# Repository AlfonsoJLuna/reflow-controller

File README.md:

# Reflow Controller

Open-source reflow controller for ovens and hot plates.

 | 
:---: | :---:
Front | Back

## Features

* MCU: STM32G030K6T6
* CH340E USB-Serial converter.
* Sensors: K-Type thermocouple to digital converter. Compatible with both MAX31855 and MAX6675.
* Display: SSD1306 128×164 0.96" OLED.
* Inputs: 4x Push buttons to navigate the menu.
* Outputs: 2x 5V 300mA outputs. Capable of driving solid state relays as well as inductive loads (mechanical relays, fans).
* Buzzer: Alarm buzzer.
* Power: 5V provided via USB-C or screw terminals.

## Related repositories

Firmware for this project lives in [reflow-controller-fw](https://github.com/AlfonsoJLuna/reflow-controller-fw).

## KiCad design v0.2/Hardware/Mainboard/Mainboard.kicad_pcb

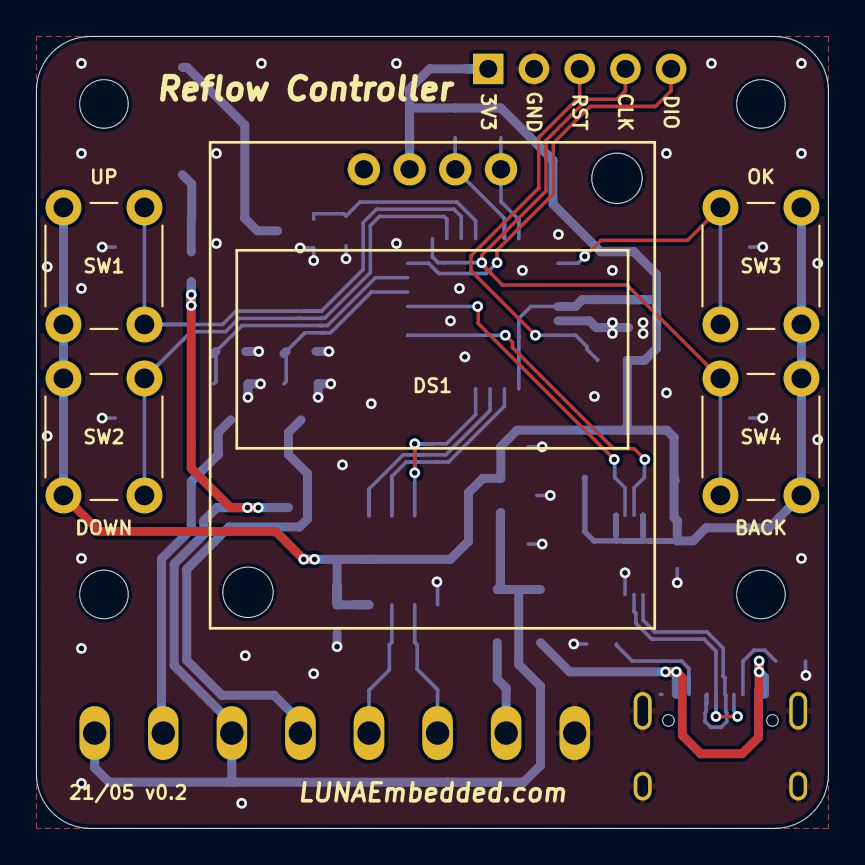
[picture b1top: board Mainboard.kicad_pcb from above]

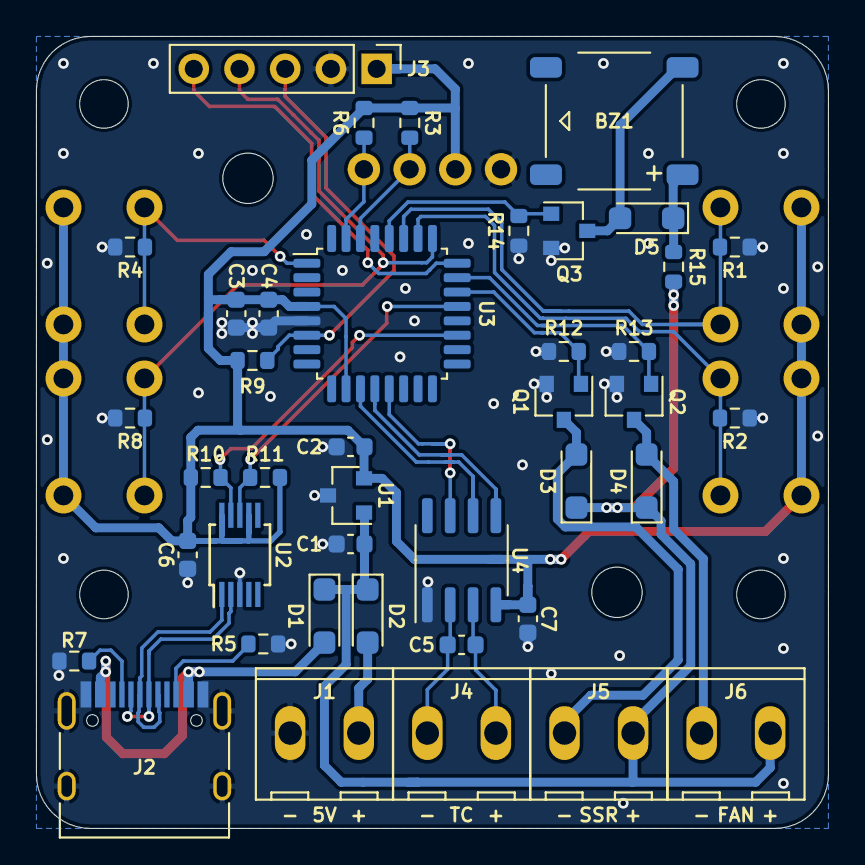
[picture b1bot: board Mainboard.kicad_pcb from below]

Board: 2 copper layers, 44.0 x 44.0 mm, 46 parts (41 on the bottom side), 31 nets.

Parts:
BZ1: MLT-7525
C1, C2, C3: 10u; C_0603_1608Metric
C4, C6, C7: 100n; C_0603_1608Metric
C5: 10n; C_0603_1608Metric
D1, D2, D3, D4, D5: MBR120VLSFT3G; SOD-123FL
DS1: SSD1306_0.96_128x64_I2C
J1: 5V; WJ124-3.81-2P
J2: TYPE-C-31-M-12; USB_C_Receptacle_HRO_TYPE-C-31-M-12
J3: Debug; PinHeader_1x05_P2.54mm_Vertical
J4: TC; WJ124-3.81-2P
J5: S1; WJ124-3.81-2P
J6: S2; WJ124-3.81-2P
Q1, Q2, Q3: BSS138P; SOT-23
R1, R2, R4, R5, R7, R8, R9, R12, R13, R14: 5K1; R_0603_1608Metric
R3, R6, R10, R11: DNP; R_0603_1608Metric
R15: 100; R_0603_1608Metric
SW1: UP; SW_PUSH_6mm_H9.5mm
SW2: DOWN; SW_PUSH_6mm_H9.5mm
SW3: OK; SW_PUSH_6mm_H9.5mm
SW4: BACK; SW_PUSH_6mm_H9.5mm
U1: AP7333-33SAG-7; SOT-23
U2: CH340E; MSOP-10_3x3mm_P0.5mm
U3: STM32G030K6T6; LQFP-32_7x7mm_P0.8mm
U4: MAX31855KASA+T; SOIC-8_3.9x4.9mm_P1.27mm

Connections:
/3V3: C2.1, C3.1, C4.1, C6.1, C7.1, DS1.2, J3.1, R3.1, R6.1, R9.2, R10.1, R11.1, SW1.1, SW2.2, SW3.2, SW4.1, U1.2, U2.7, U2.10, U3.4, U3.10, U4.4
/5V: C1.1, D1.1, D2.1, D3.1, D4.1, J5.2, J6.2, R15.1, U1.1
/BTN_BACK: J3.4, R8.1, SW4.2, U3.25
/BTN_DOWN: R2.1, SW2.1, U3.26
/BTN_OK: R4.1, SW3.1, U3.1
/BTN_UP: R1.1, SW1.2, U3.27
/BUZZER+: BZ1.1, D5.1, R15.2
/BUZZER-: BZ1.2, D5.2, Q3.3
/CC1: J2.A5, R7.1
/CC2: J2.B5, R5.1
/I2C_SCL: DS1.3, R3.2, U3.30
/I2C_SDA: DS1.4, R6.2, U3.31
/MCU_RXD: R11.2, U2.8, U3.21
/MCU_TXD: R10.2, U2.9, U3.19
/NRST: J3.3, R9.1, U3.6
/OUT_FAN: Q2.1, R13.1, U3.23
/OUT_FAN-: D4.2, J6.1, Q2.3
/OUT_SSR: Q1.1, R12.1, U3.22
/OUT_SSR-: D3.2, J5.1, Q1.3
/PWM_BUZZER: Q3.1, R14.1, U3.28
/SPI_CS: U3.11, U4.6
/SPI_MISO: U3.13, U4.7
/SPI_SCK: U3.12, U4.5
/SWDIO: J3.5, U3.24
/T+: C5.1, J4.2, U4.3
/T-: C5.2, J4.1, U4.2
/USB_DM: J2.A7, J2.B7, U2.2
/USB_DP: J2.A6, J2.B6, U2.1
/VIN: D2.2, J1.2
/VUSB: D1.2, J2.A4, J2.A9, J2.B4, J2.B9
GND: C1.2, C2.2, C3.2, C4.2, C6.2, C7.2, DS1.1, J1.1, J2.A1, J2.A12, J2.B1, J2.B12, J2.S1, J3.2, Q1.2, Q2.2, Q3.2, R1.2, R2.2, R4.2, R5.2, R7.2, R8.2, R12.2, R13.2, R14.2, U1.3, U2.3, U3.5, U4.1

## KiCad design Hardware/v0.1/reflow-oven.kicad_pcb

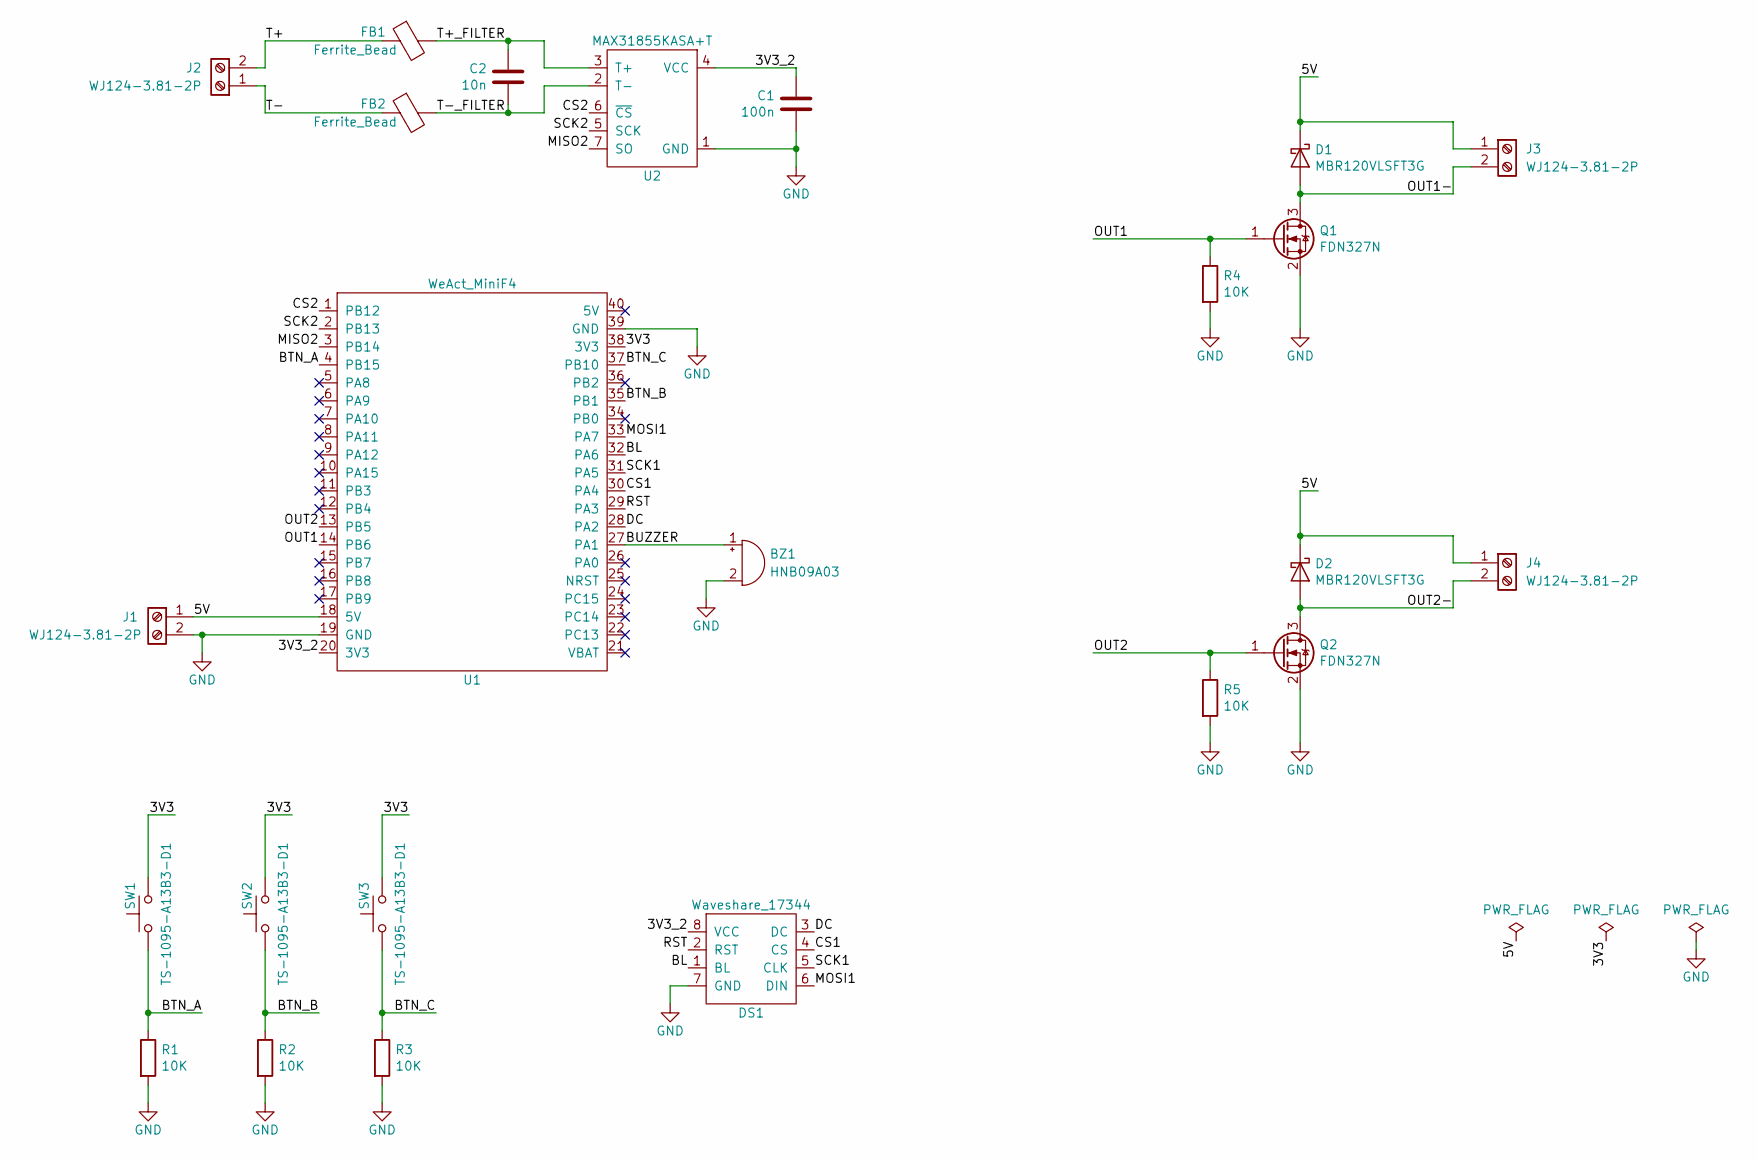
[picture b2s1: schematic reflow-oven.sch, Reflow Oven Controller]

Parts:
BZ1: HNB09A03; MPN HNB09A03
C1: 100n; C_0603_1608Metric; MPN CL10B104KB8NNNC
C2: 10n; C_0603_1608Metric; MPN CL10B103KB8NNNC
D1, D2: MBR120VLSFT3G; SOD-123FL; MPN MBR120VLSFT3G
DS1: Waveshare_17344; MPN Waveshare_17344
FB1, FB2: Ferrite_Bead; L_0603_1608Metric; MPN DNP
J1, J2, J3, J4: WJ124-3.81-2P; MPN WJ124-3.81-2P
Q1, Q2: FDN327N; SOT-23; MPN FDN327N
R1, R2, R3, R4, R5: 10K; R_0603_1608Metric; MPN RC0603FR-0710KL
SW1, SW2, SW3: TS-1095-A13B3-D1; SW_PUSH_6mm_H9.5mm; MPN TS-1095-A13B3-D1
U1: WeAct_MiniF4; MPN WeAct_MiniF4_STM32F411CEU6
U2: MAX31855KASA+T; SOIC-8_3.9x4.9mm_P1.27mm; MPN MAX31855KASA+T

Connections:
/3V3: SW1.2, SW2.2, SW3.2, U1.38 (3V3)
/3V3_2: C1.1, DS1.8 (VCC), U1.20 (3V3), U2.4 (VCC)
/5V: D1.1 (K), D2.1 (K), J1.1, J3.1, J4.1, U1.18 (5V)
/BL: DS1.1 (BL), U1.32 (PA6)
/BTN_A: R1.1, SW1.1, U1.4 (PB15)
/BTN_B: R2.1, SW2.1, U1.35 (PB1)
/BTN_C: R3.1, SW3.1, U1.37 (PB10)
/BUZZER: BZ1.1 (-), U1.27 (PA1)
/CS1: DS1.4 (CS), U1.30 (PA4)
/CS2: U1.1 (PB12), U2.6 (~CS~)
/DC: DS1.3 (DC), U1.28 (PA2)
/MISO2: U1.3 (PB14), U2.7 (SO)
/MOSI1: DS1.6 (DIN), U1.33 (PA7)
/OUT1: Q1.1 (G), R4.1, U1.14 (PB6)
/OUT1-: D1.2 (A), J3.2, Q1.3 (D)
/OUT2: Q2.1 (G), R5.1, U1.13 (PB5)
/OUT2-: D2.2 (A), J4.2, Q2.3 (D)
/RST: DS1.2 (RST), U1.29 (PA3)
/SCK1: DS1.5 (CLK), U1.31 (PA5)
/SCK2: U1.2 (PB13), U2.5 (SCK)
/T+: FB1.1, J2.2
/T+_FILTER: C2.1, FB1.2, U2.3 (T+)
/T-: FB2.1, J2.1
/T-_FILTER: C2.2, FB2.2, U2.2 (T-)
GND: BZ1.2 (+), C1.2, DS1.7 (GND), J1.2, Q1.2 (S), Q2.2 (S), R1.2, R2.2, R3.2, R4.2, R5.2, U1.19 (GND), U1.39 (GND), U2.1 (GND)

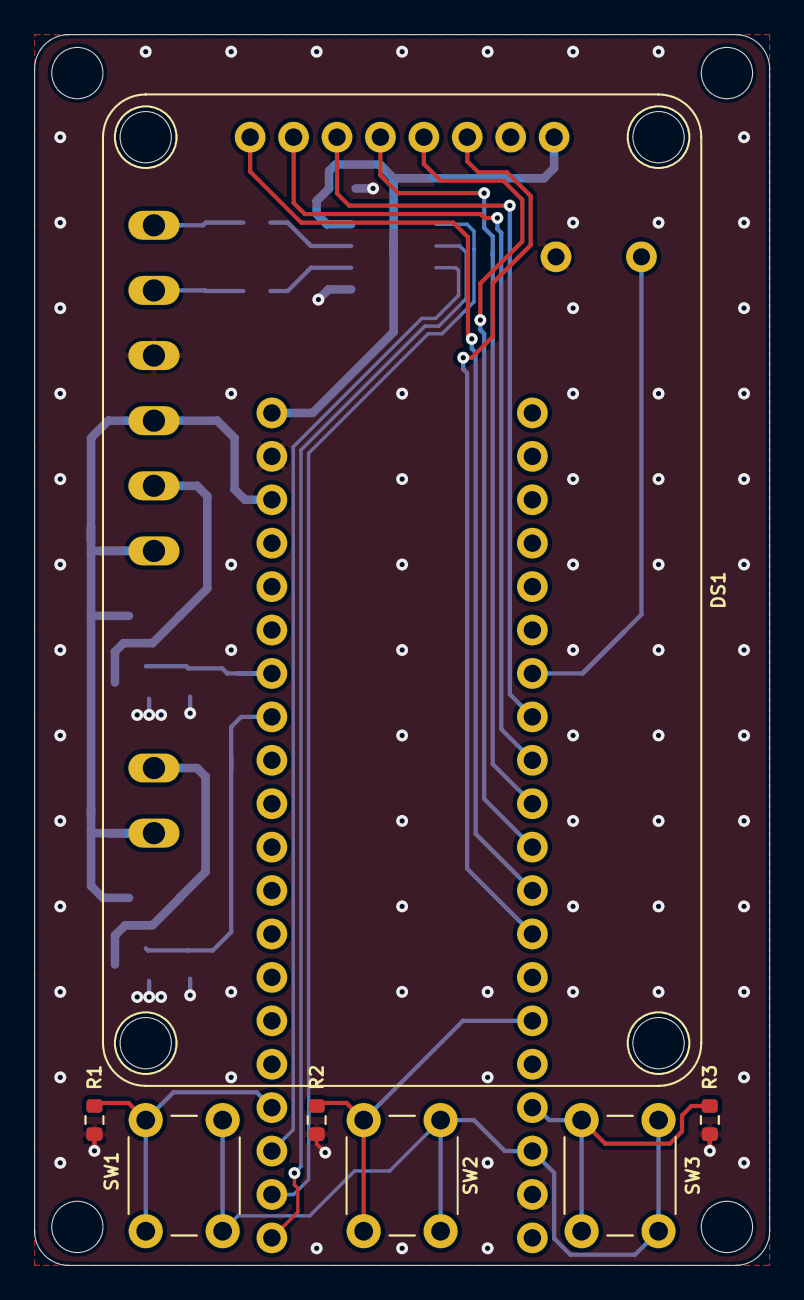
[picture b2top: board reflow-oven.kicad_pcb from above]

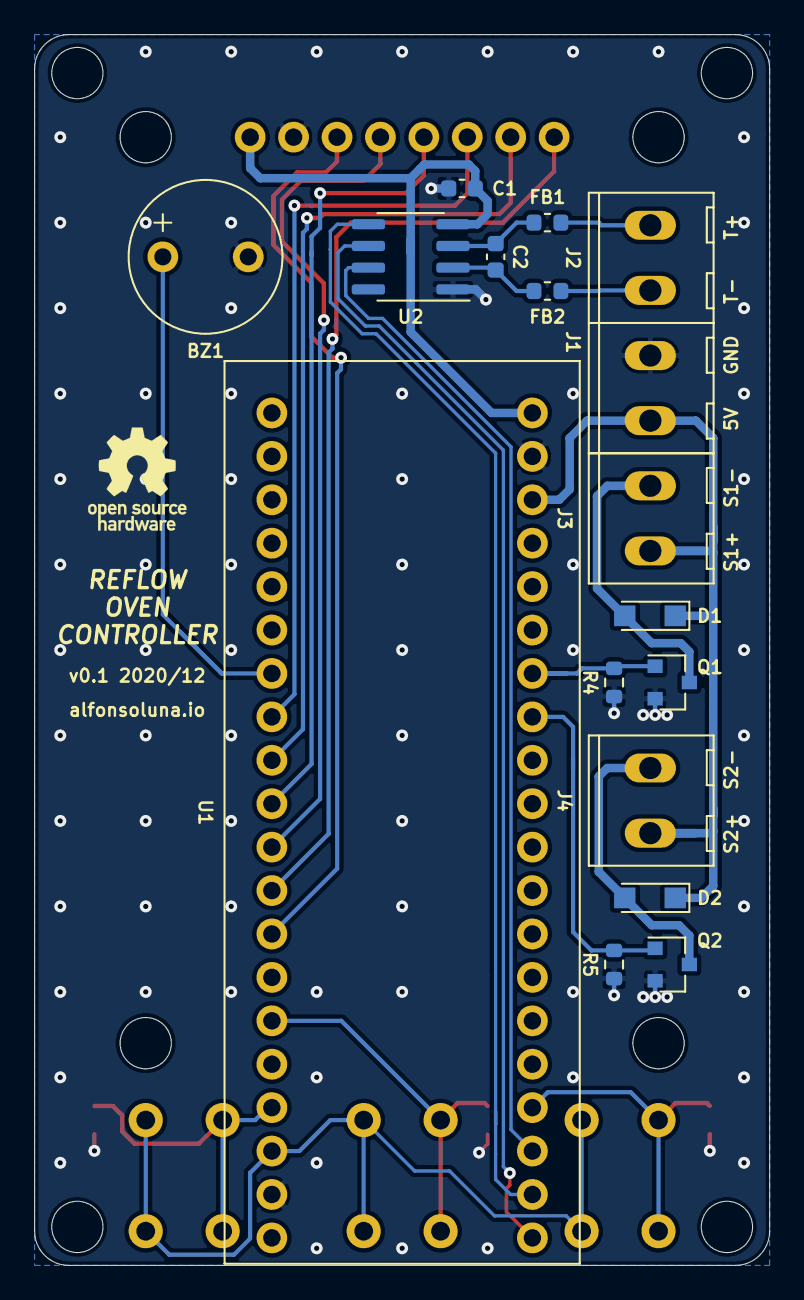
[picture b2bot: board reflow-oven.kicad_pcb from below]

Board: 2 copper layers, 43.0 x 72.0 mm, 24 parts (17 on the bottom side), 25 nets.

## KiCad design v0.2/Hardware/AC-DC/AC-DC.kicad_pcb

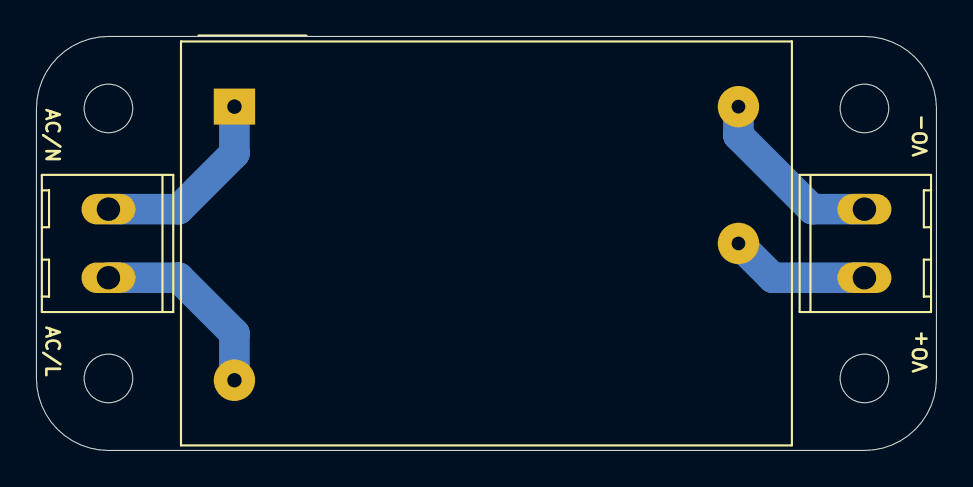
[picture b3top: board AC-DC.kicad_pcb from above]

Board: 2 copper layers, 50.0 x 23.0 mm, 4 parts (1 on the bottom side), 4 nets.

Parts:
J1, J2: WJ124-3.81-2P
PS1: IRM-02-5; Converter_ACDC_MeanWell_IRM-02-xx_THT
r: OSHW-Logo_5.7x6mm_SilkScreen

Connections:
GND: J2.2, PS1.3
unnamed: J1.1, PS1.1
unnamed: J1.2, PS1.2
unnamed: J2.1, PS1.4

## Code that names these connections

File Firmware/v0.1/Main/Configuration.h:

#ifndef CONFIGURATION_H
#define CONFIGURATION_H


//////////////////////////////////////////////////
// Temperature sensor selection
//////////////////////////////////////////////////


#define USE_MAX31855
// #define USE_MAX6675


//////////////////////////////////////////////////
// Temperature reading offset (ºC)
//////////////////////////////////////////////////


#define TEMP_OFFSET 0


//////////////////////////////////////////////////
// Enable or disable the buzzer
//////////////////////////////////////////////////


#define BUZZER_EN 0


//////////////////////////////////////////////////
// PID parameters
//////////////////////////////////////////////////


#define PID_KP 50
#define PID_KI 25
#define PID_KD 0


//////////////////////////////////////////////////
// Pin definitions
//////////////////////////////////////////////////


#define MAXDO   PB14
#define MAXCS   PB12
#define MAXCLK  PB13

#define BUZZ    PA1
#define OUT1    PB6
#define OUT2    PB5

#define BTNA    PB15
#define BTNB    PB1
#define BTNC    PB10

#define LCDDO   PA7
#define LCDCS   PA4
#define LCDCLK  PA5
#define LCDRST  PA3
#define LCDDC   PA2
#define LCDBL   PA6


#endif

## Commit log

2020-12-24 Finished schematics
2020-12-25 Finished PCB layout
2021-01-23 Added pdf schematics
2021-02-19 Added initial firmware files
2021-02-22 Added configuration.h with pin defines and options
2021-02-22 Added support for MAX6675
2021-02-22 Use Configuration.h defines
2021-02-22 Updated readme, added interactive BOM
2021-02-22 Updated interactive BOM link
2021-02-23 Refactoring
2021-02-23 Retrieve profile names for the menu
2021-02-23 Configurable temperature offset
2021-02-25 Added bit-banged 1Hz PWM outputs
2021-02-25 Aesthetic changes
2021-02-27 Added PID control
2021-02-27 Fixed anti wind-up
2021-02-28 Added buzzer functionality, improved readme
2021-03-03 Added enclosure FreeCAD and STL files
2021-03-29 Improved profiles and cooldown handling
2021-04-07 Improved profiles, configurable buzzer beeps
2021-04-09 Improved default PID parameters, added PID tuner, added Simulink model
2021-04-11 Added AC/DC module
2021-04-26 v0.2: Finished schematics
2021-04-26 v0.2: Preliminary placement
2021-04-28 v0.2: Updated placement
2021-05-04 v0.2: Finished PCBs
2021-05-04 v0.2: KiKit panels
2021-05-05 v0.2: Modified Uyue-946-1010 front panel
2021-10-28 v0.1: Thermocouple error handling
2022-01-21 v0.1: Updated MAX31855 and MAX6675 SPI driver so the temperature can be read even in presence of TC shorted to GND/VCC errors
2022-01-23 v0.1: Updated profiles for better results
2026-04-24 Updated readme after the split
2026-04-24 Updated folder structure
2026-04-25 Removed v0.1 files as now there is a v0.1 tag
2026-04-25 Updated project files to KiCad 10
2026-04-25 Updated readme and images

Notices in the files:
Hardware/v0.1/reflow-oven.sch:
Licensed under CERN OHL v1.2
